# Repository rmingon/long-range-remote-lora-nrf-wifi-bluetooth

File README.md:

# **Triple-Radio Remote Controller PCB**

A compact, hand-held remote that combines **Wi-Fi / Bluetooth (ESP32)**, **2.4 GHz nRF24L01+** and **868/915 MHz LoRa (RFM95W)** in a single, joystick-style board.  
It is intended as a flexible radio interface for robotics, drones, RC models, telemetry links or IoT experimentation where different wireless technologies are useful at once.

|  |  |
| ----------------------------- | ------------------------------ |

---

## Table of Contents
1. [Features](#features)  
2. [Hardware Overview](#hardware-overview)  
3. [Schematic Blocks](#schematic-blocks)  
4. [Power Architecture](#power-architecture)  
5. [Pin Map](#pin-map)  
6. [Firmware](#firmware)  
7. [Getting Started](#getting-started)  
8. [Directory Layout](#directory-layout)  
9. [Road-Map](#road-map)  
10. [License](#license)

---

## Features
* **MCU — ESP32-WROOM-32**  
  * Dual-core Xtensa @ 240 MHz, 520 KB SRAM  
  * Integrated Wi-Fi 802.11 b/g/n + Bluetooth Classic/LE  
* **Radios**  
  * **nRF24L01+** – 2.4 GHz packet radio via 8-pin vertical socket  
  * **RFM95W** – Semtech SX1276 LoRa transceiver, SMA edge connector (keep-out ensured)  
* **Controls**  
  * Dual analog thumb joysticks (SparkFun COM-09032) with push-buttons  
  * One user LED (GPIO-controlled)  
* **Sensors**  
  * **MPU-6050** 6-axis IMU (gyro + accel)  
  * **BMP-280** barometric pressure / temperature sensor  
* **USB & Programming**  
  * On-board CH340C USB-to-UART with auto-reset/boot circuitry  
  * Standard USB-C connector (5 V input & data)  
* **Power**  
  * 2-pin JST-PH for Li-Ion/Li-Po battery (“+BATT”)  
  * AMS1117-3 V3 LDO for logic / radios  
  * AMS1117-5 V rail for external accessories (ESC, servos, etc.)  
  * Reverse-polarity and inrush-limit protections  
* **Expansion / Debug**  
  * 5-pin 5 V UART header  
  * 4-pin 5 V I²C header  
  * Plenty of un-populated GPIO test-pads on bottom layer  
* Finished board: **74 mm × 74 mm**, 2-layer, ENIG, green solder-mask.

---

## Hardware Overview

| Block | Purpose | Interfaces |
|-------|---------|------------|
| ESP32-WROOM-32 | Central MCU; Wi-Fi/BLE | SPI, I²C, UART, ADC |
| RFM95W-868/915 | Long-range LoRa | SPI (SCK/MISO/MOSI/SS) + DIO0/1/2 + RESET |
| nRF24L01+ socket | Low-latency 2.4 GHz | Same SPI bus, CE/CSN/IRQ lines |
| MPU-6050 | Motion sensing | I²C @ 400 kHz |
| BMP-280 | Altitude / temp | I²C (wired for I²C) |
| Dual joysticks | User input | 4 × ADC + 2 × GPIO (switches) |
| CH340C | USB-UART | UART 0 (TX0/RX0), DTR/RTS auto reset |
| AMS1117-3 V3 | Logic 3.3 V rail | Up to 1 A |
| AMS1117-5 V | Aux 5 V rail | Up to 1 A |

---

## Power Architecture
```
Li-Po 2S
        │
        ├─ AMS1117-5 V ───► 5 V header / accessories
        │
        └─ AMS1117-3 V3 ──► ESP32, sensors, radios (on-board)
```
The micro-USB port supplies 5 V when plugged; if a battery is present it is **not charged** – add an external charger if required.

---

## Pin Map

| Signal | ESP32 GPIO | Notes |
|--------|-----------|-------|
| **LoRa (RFM95W)** |||
| LORA_SS (NSS) | 5 | Shared SPI SS |
| LORA_RST | 26 | Active-low reset |
| LORA_DIO0 | 34 | IRQ – input-only |
| LORA_DIO1 | 35 | Optional |
| **nRF24L01+** |||
| NRF_SS (CSN) | 33 |
| NRF_CE | 32 |
| NRF_IRQ | 27 |
| **Shared SPI bus** |||
| SCK | 18 |
| MOSI | 23 |
| MISO | 19 |
| **I²C bus** |||
| SDA | 21 | MPU-6050, BMP-280, external header |
| SCL | 22 |
| **Joysticks** |||
| Stick-L H | 36 (ADC1_0) |
| Stick-L V | 39 (ADC1_3) |
| Stick-R H | 34 (ADC1_6) |
| Stick-R V | 35 (ADC1_7) |
| Stick-L Btn | 13 |
| Stick-R Btn | 12 |
| **USB-UART** |||
| TX0 | 1 |
| RX0 | 3 |
| DTR / RTS | Auto-reset circuit |

All unused pins are broken out to pads for hacking.

---

## Firmware

Any ESP32 framework will work; the board is tested with **PlatformIO + Arduino**.  
Example `platformio.ini` snippet:

```ini
[env:esp32-remote]
platform      = espressif32
board         = esp32dev
framework     = arduino
monitor_speed = 115200
build_flags   =
  -D LORA_SS=5
  -D LORA_RST=26
  -D LORA_DIO0=34
  -D NRF_CE=32
  -D NRF_CS=33
  -D NRF_IRQ=27
lib_deps =
  sandeepmistry/LoRa
  maniacbug/RF24
  adafruit/Adafruit MPU6050
  adafruit/Adafruit BMP280 Library
```

---

## Getting Started

1. **Clone** the repository  

   ```bash
   git clone git@github.com:rmingon/long-range-remote-lora-nrf-wifi-bluetooth.git
   cd long-range-remote-lora-nrf-wifi-bluetooth
   ```

2. **Install PlatformIO** (VS Code extension or CLI).  
3. **Select the env** in `platformio.ini`, edit radio pins if you changed the board.  
4. **Connect micro-USB** ch340 auto-programming.  
5. Verify serial output at **115 200 baud**.

### LoRa / nRF24L01+ demos
Example sketches are in `firmware/examples/`:

* `lora_ping/` – bidirectional ping using SX1276  
* `rf24_controller/` – joystick values sent every 20 ms to a base-station  
* `wifi_update/` – OTA update via Wi-Fi AP  

Build & flash with:

```bash
pio run -e esp32-remote -t upload -d firmware/examples/lora_ping
```

---

## Directory Layout
```
.
├─ firmware/              → PlatformIO source
├─ hardware/
│  ├─ kicad/              → .kicad_pcb, .sch, libraries
│  ├─ gerber/             → ready for fabrication
│  └─ stl/                → optional enclosure models
├─ docs/
│  ├─ img/                → renders & photos used in README
│  └─ datasheets/
└─ LICENSE
```

---

## Road-Map
* Li-Po charging / fuel-gauge on-board  
* Hall-effect joysticks option  
* Enclosure with TPU grips  
* Support for 900 MHz nRF905 as fourth radio

---

## License
Hardware is released under **CERN-OHL-S v2**.  
Firmware samples are **MIT**.  
See individual source files for details.

---

*If you make something cool with this board, please open a pull-request and show it off!*

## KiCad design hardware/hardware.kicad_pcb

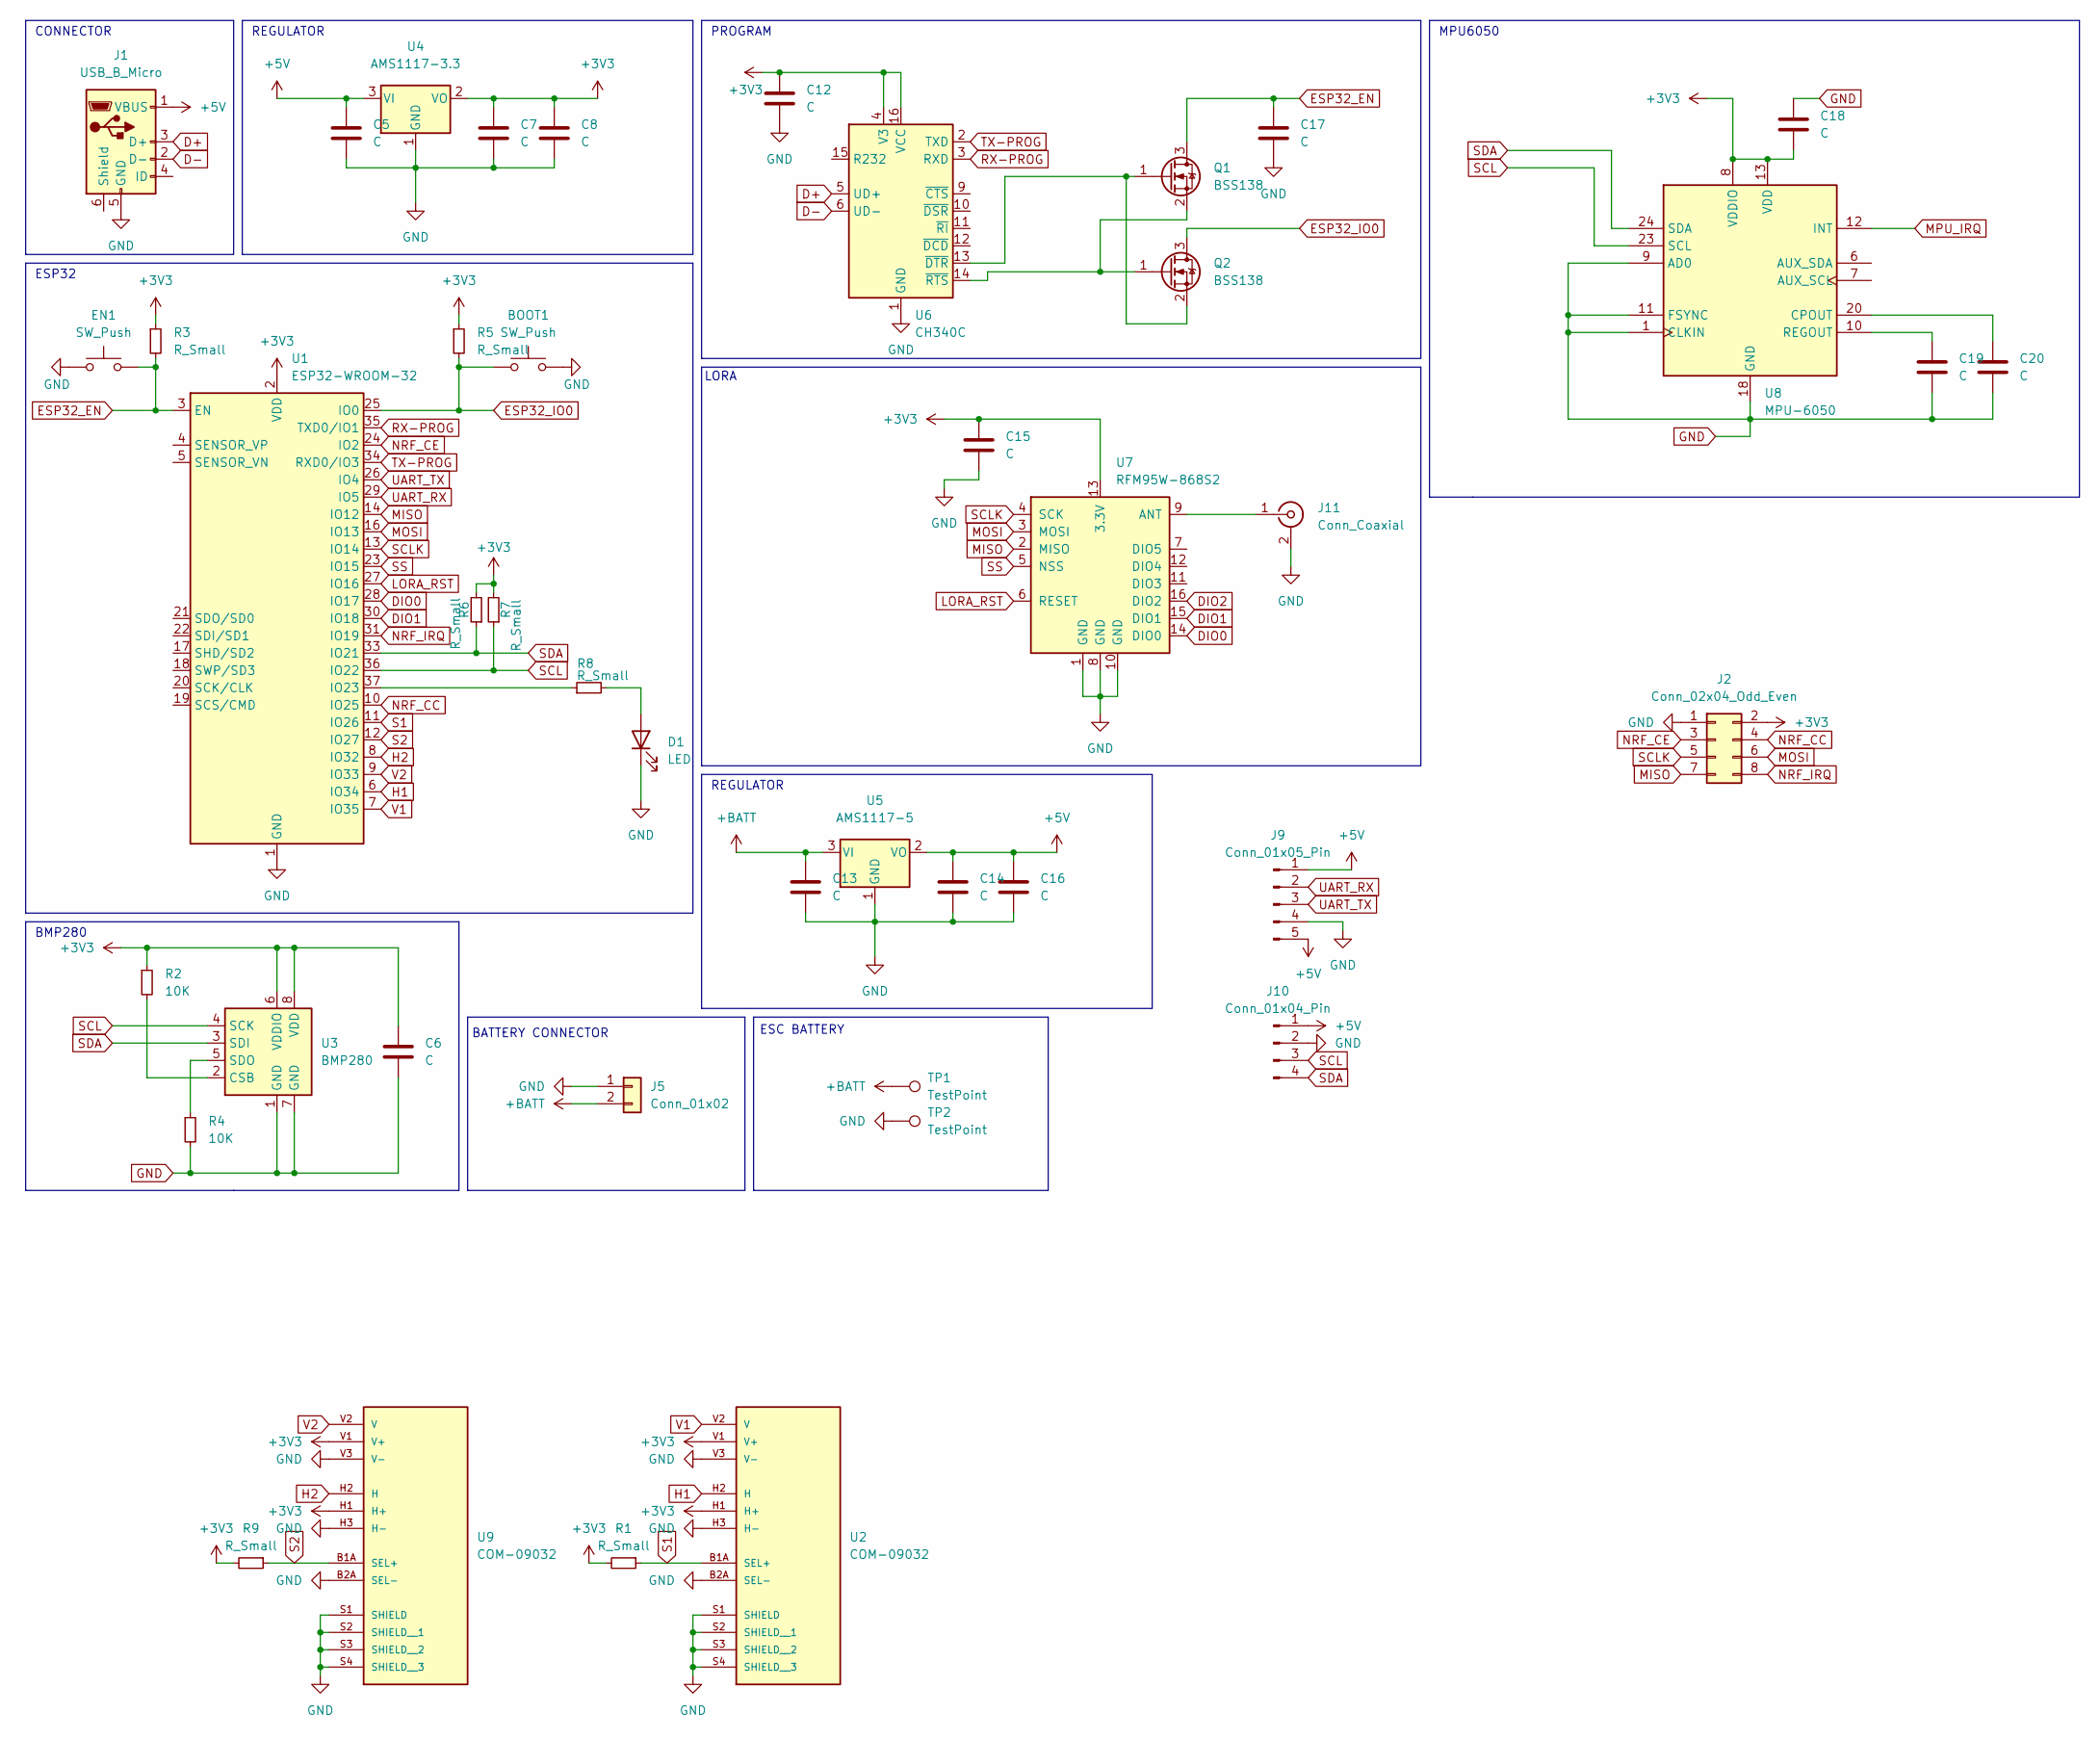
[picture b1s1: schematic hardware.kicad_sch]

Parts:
BOOT1: SW_Push; SW_SPST_FSMSM
C5, C6, C7, C8, C12, C13, C14, C15, C16, C17, C18, C19, C20: C; C_0603_1608Metric
D1: LED; LED_0603_1608Metric
EN1: SW_Push; SW_SPST_FSMSM
J1: USB_B_Micro; USB_Micro-B_Amphenol_10118194_Horizontal
J2: Conn_02x04_Odd_Even; PinHeader_2x04_P2.54mm_Vertical
J5: Conn_01x02; AMASS_XT30U-F_1x02_P5.0mm_Vertical
J9: Conn_01x05_Pin; PinHeader_1x05_P2.54mm_Vertical
J10: Conn_01x04_Pin; PinHeader_1x04_P2.54mm_Vertical
J11: Conn_Coaxial; SMA_Samtec_SMA-J-P-H-ST-EM1_EdgeMount
Q1, Q2: BSS138; SOT-23
R1, R3, R5, R6, R7, R8, R9: R_Small; R_0603_1608Metric
R2, R4: 10K; R_0603_1608Metric
TP1, TP2: TestPoint; TestPoint_Pad_2.5x2.5mm
U1: ESP32-WROOM-32
U2, U9: COM-09032; XDCR_COM-09032; PARTREV N/A
U3: BMP280; Bosch_LGA-8_2x2.5mm_P0.65mm_ClockwisePinNumbering
U4: AMS1117-3.3; SOT-223-3_TabPin2
U5: AMS1117-5; SOT-223-3_TabPin2
U6: CH340C; SOIC-16_3.9x9.9mm_P1.27mm
U7: RFM95W-868S2; HOPERF_RFM9XW_SMD
U8: MPU-6050; InvenSense_QFN-24_4x4mm_P0.5mm

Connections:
+3V3: C6.1, C7.1, C8.1, C12.1, C15.1, C18.2, J2.2, R1.2, R2.1, R3.1, R5.1, R6.2, R7.2, R9.2, U1.2 (VDD), U2.H1 (H+), U2.V1 (V+), U3.6 (VDDIO), U3.8 (VDD), U4.2 (VO), U6.4 (V3), U6.16 (VCC), U7.13 (3.3V), U8.8 (VDDIO), U8.13 (VDD), U9.H1 (H+), U9.V1 (V+)
+5V: C5.1, C14.1, C16.1, J1.1 (VBUS), J9.1, J9.5, J10.1, U4.3 (VI), U5.2 (VO)
+BATT: C13.1, J5.2, TP1.1, U5.3 (VI)
D+: J1.3 (D+), U6.5 (UD+)
D-: J1.2 (D-), U6.6 (UD-)
DIO0: U1.28 (IO17), U7.14 (DIO0)
DIO1: U1.30 (IO18), U7.15 (DIO1)
DIO2: U7.16 (DIO2)
ESP32_EN: C17.1, EN1.2, Q1.3 (D), R3.2, U1.3 (EN)
ESP32_IO0: BOOT1.1, Q2.3 (D), R5.2, U1.25 (IO0)
GND: BOOT1.2, C5.2, C6.2, C7.2, C8.2, C12.2, C13.2, C14.2, C15.2, C16.2, C17.2, C18.1, C19.2, C20.2, D1.1 (K), EN1.1, J1.5 (GND), J2.1, J5.1, J9.4, J10.2, J11.2 (Ext), R4.2, TP2.1, U1.1 (GND), U1.15 (GND), U1.38 (GND), U1.39 (GND), U2.B2A (SEL-), U2.H3 (H-), U2.S1 (SHIELD), U2.S2 (SHIELD__1), U2.S3 (SHIELD__2), U2.S4 (SHIELD__3), U2.V3 (V-), U3.1 (GND), U3.7 (GND), U4.1 (GND), U5.1 (GND), U6.1 (GND), U7.1 (GND), U7.8 (GND), U7.10 (GND), U8.1 (CLKIN), U8.9 (AD0), U8.11 (FSYNC), U8.18 (GND), U9.B2A (SEL-), U9.H3 (H-), U9.S1 (SHIELD), U9.S2 (SHIELD__1), U9.S3 (SHIELD__2), U9.S4 (SHIELD__3), U9.V3 (V-)
H1: U1.6 (IO34), U2.H2 (H)
H2: U1.8 (IO32), U9.H2 (H)
LORA_RST: U1.27 (IO16), U7.6 (RESET)
MISO: J2.7, U1.14 (IO12), U7.2 (MISO)
MOSI: J2.6, U1.16 (IO13), U7.3 (MOSI)
MPU_IRQ: U8.12 (INT)
NRF_CC: J2.4, U1.10 (IO25)
NRF_CE: J2.3, U1.24 (IO2)
NRF_IRQ: J2.8, U1.31 (IO19)
unnamed: D1.2 (A), R8.2
unnamed: J11.1 (In), U7.9 (ANT)
unnamed: Q1.1 (G), Q2.2 (S), U6.13 (~DTR)
unnamed: Q1.2 (S), Q2.1 (G), U6.14 (~RTS)
unnamed: R8.1, U1.37 (IO23)
unnamed: R2.2, U3.2 (CSB)
unnamed: R4.1, U3.5 (SDO)
unnamed: C20.1, U8.20 (CPOUT)
unnamed: C19.1, U8.10 (REGOUT)
RX-PROG: U1.35 (TXD0/IO1), U6.3 (RXD)
S1: R1.1, U1.11 (IO26), U2.B1A (SEL+)
S2: R9.1, U1.12 (IO27), U9.B1A (SEL+)
SCL: J10.3, R7.1, U1.36 (IO22), U3.4 (SCK), U8.23 (SCL)
SCLK: J2.5, U1.13 (IO14), U7.4 (SCK)
SDA: J10.4, R6.1, U1.33 (IO21), U3.3 (SDI), U8.24 (SDA)
SS: U1.23 (IO15), U7.5 (NSS)
TX-PROG: U1.34 (RXD0/IO3), U6.2 (TXD)
UART_RX: J9.2, U1.29 (IO5)
UART_TX: J9.3, U1.26 (IO4)
V1: U1.7 (IO35), U2.V2 (V)
V2: U1.9 (IO33), U9.V2 (V)

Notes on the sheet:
CONNECTOR
REGULATOR
MPU6050
BMP280
ESC BATTERY
LORA
PROGRAM
ESP32
BATTERY CONNECTOR

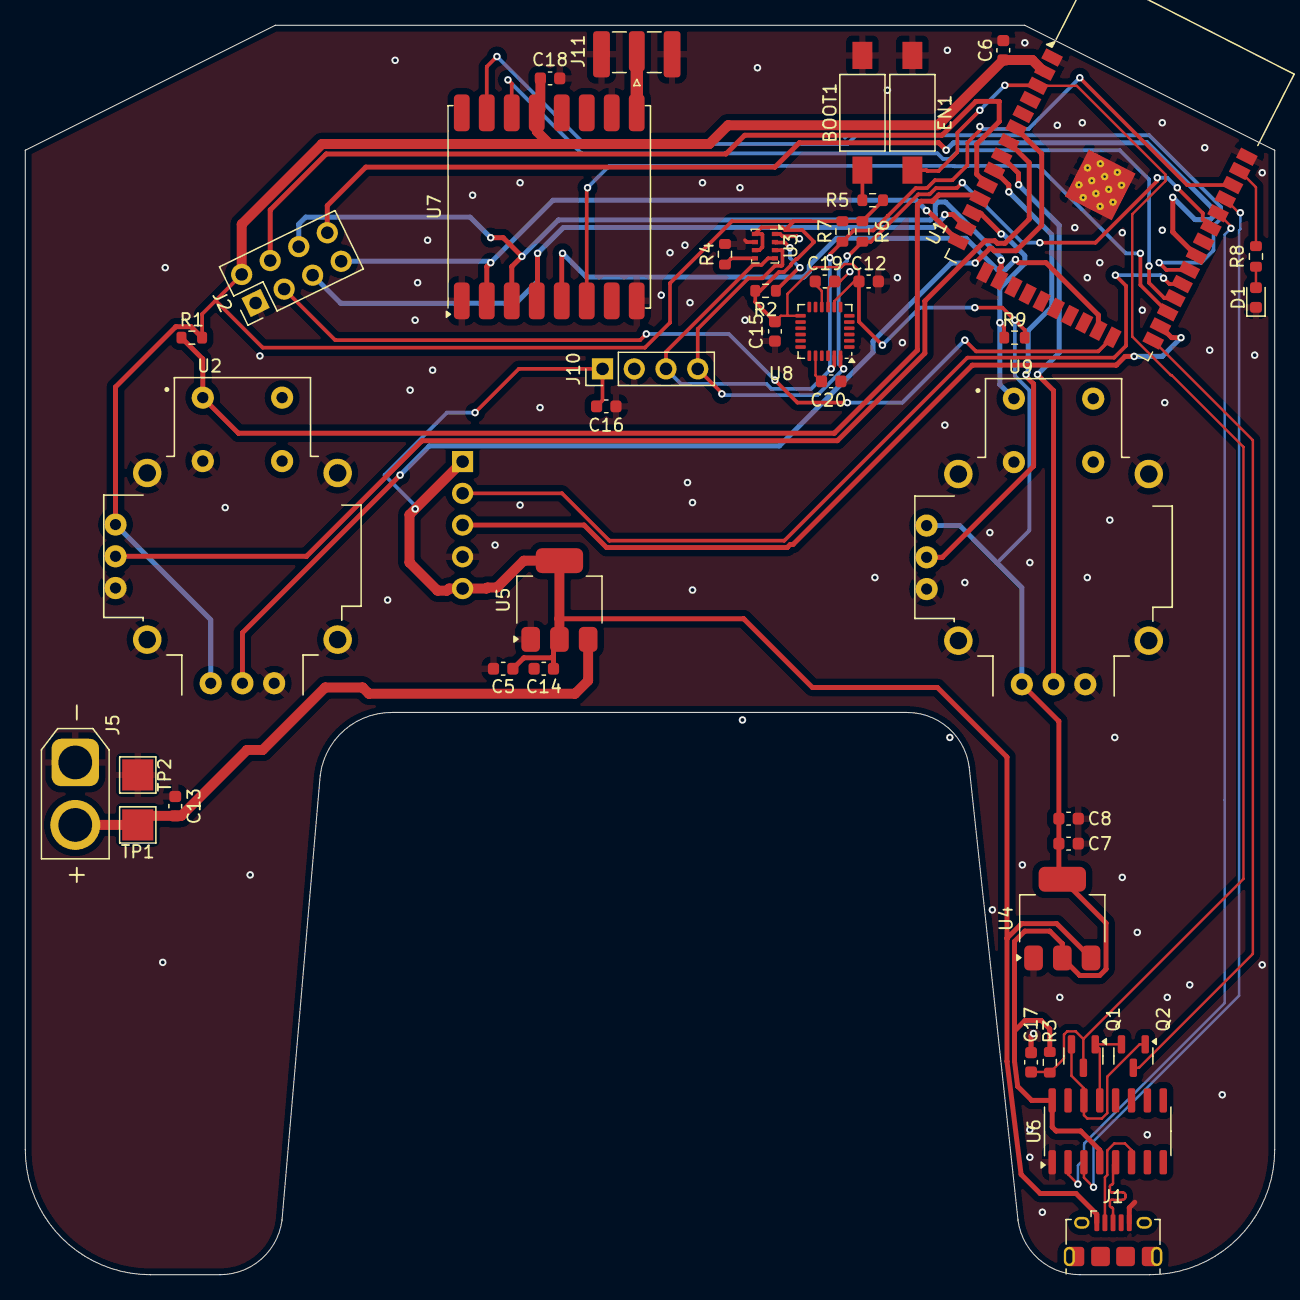
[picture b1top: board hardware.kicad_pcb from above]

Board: 2 copper layers, 100.0 x 100.0 mm, 44 parts (1 on the bottom side), 39 nets.

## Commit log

2025-06-29 wiring + pcb + componants
2025-06-29 add pictures
2025-06-29 add readme
2025-06-29 update readme gitclone
2025-06-29 move picture + update doc
2025-06-30 update pcb size
2025-07-11 add web interface
2025-07-11 add minimal code
